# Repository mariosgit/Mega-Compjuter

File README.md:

# MEGA CompJU+TEr

# Status

Just an Idee. Made a basic PCB. Started experimenting...

# Wath's this ?

Arduino MEGA Shield with a UB8830 on top. The UB8833 is a Ostblock version of a Zilog Z8682 with a view quirks.

A bit like these things... http://8bitforce.com/projects/retroshield/ [Or here the Z80 code](https://gitlab.com/8bitforce/retroshield-arduino/-/blob/master/kz80/kz80_test/kz80_test.ino?ref_type=heads)

### Bugs / Improvements

* UB8833 reset(pin6) to some pin(45) ! keep it low until all ports initialize.
* LEDs for AS,RW,DS ?
* Fuse ? The Z8 needs 180mA !?

# Software

From Z8 datasheet...

* When AS goes LOW->HI latch the low adr byte. And read and keep RW flag.
* When DS goes HIGH->LOW and RW is reading (HIGH) put data on the bus. 
* When DS goes low and writing, read the data, do something e.g. save to ram.
* Turn of Data output ??? When ??? Read data to DS 1 hold time is 0, so turn it off after DS goes high.

### Reset

8833 RESET-Eingang (vgl . Kapitel 1) .
Hat er nach eingeschwungene r
Spannungs- und Taktversorgun g
für mindestens **18** Taktperiode n
Nullpegel, erzeugt er im Innere n
des Einchip-Mikrorechners einige
festgelegte Zustände . 

in kurzes Pro-
gramm ab %000C im Test-ROM
konfiguriert Port 0, Port 1 und
P34 für den Anschluß des exter-
nen Speichers und springt au f
Adresse %0812

Der UB 8830 D
(UB 8831 D) besitzt auch be i
„normalem” Rücksetzen die ge-
nannten Interruptvektoren un d
springt auf die Adresse %0812,
wenn dort kein RAM bestückt is t
und P32 keine Verbindung zu P35
hat. 

Der Einchip-
Mikrorechner besitzt ein Test-
programm im internen ROM,
das sich für unsere Zwecke gut
ausnutzen läßt. Damit es vom
Prozessor ausgeführt wird, muß
eine Drahtbrücke die Port
Anschlüsse P32 und P35 ver-
binden. .......  0-Impulse
mit einer Breite von 11 μs
erscheinen. Jede Abweichung
von dieser Regel deutet auf
eine Fehlverbindung zwischen
benachbarten Leiterzügen. Bei
Inbetriebnahme mit Kopfhörer
o. ä. müssen diese 16 An-
schlüsse mit gleichlauten 5,45-
kHz-Tönen 

Der laeuft mit 8mhz, auf dem Arduino mit 70khz, Faktor 114, 1254us.

### First something ?

after applying reset for at least 3 clocks it started doing things
* AS, DS, RW go up and down
* But no data on the bus !? -> could the thing be running it's internal ROM first ? Then there should be a addr=0x0800 (ext reset vector) comming up some time.. When it reads 0 it would start @0 again ???
* Oszi say it starts reading and writing to 0x1012 after about 173 initial clocks. it writes 0xff ?

# PCB

| ATMega Pin Port | UB8833 | Comments |
|---|---|---|
| PA | AdrHi | hi adr byte |
| PC | AdrLow/Data bus | multiplexed Data/Adr bus |
| | | |
| D2(int0) | AS | Adr strobe, Lo->Hi store the low adr |
| D3(int1) | DS | Data strobe, ?? |
| | | |
| D46/PL3(pwm pin) | XTAL | Clock |
| D47/PL2 | RW | Read/Write indication |

| ATMega Pin | Display |
|---|---|
| D53 | CS |
| D49 | DC |
| D51(mosi) | DI |
| D52(sclk) | CLK |

# Refs

https://github.com/boert/JU-TE-Computer

https://hc-ddr.hucki.net/wiki/doku.php/tiny/dokumentation 

https://www.robotrontechnik.de/html/forum/thwb/showtopic.php?threadid=16374

https://hackaday.com/2020/07/17/a-z80-board-with-very-few-parts/

http://bitsavers.informatik.uni-stuttgart.de/components/zilog/z8/Z8681_Data_Sheet_Mar83.pdf

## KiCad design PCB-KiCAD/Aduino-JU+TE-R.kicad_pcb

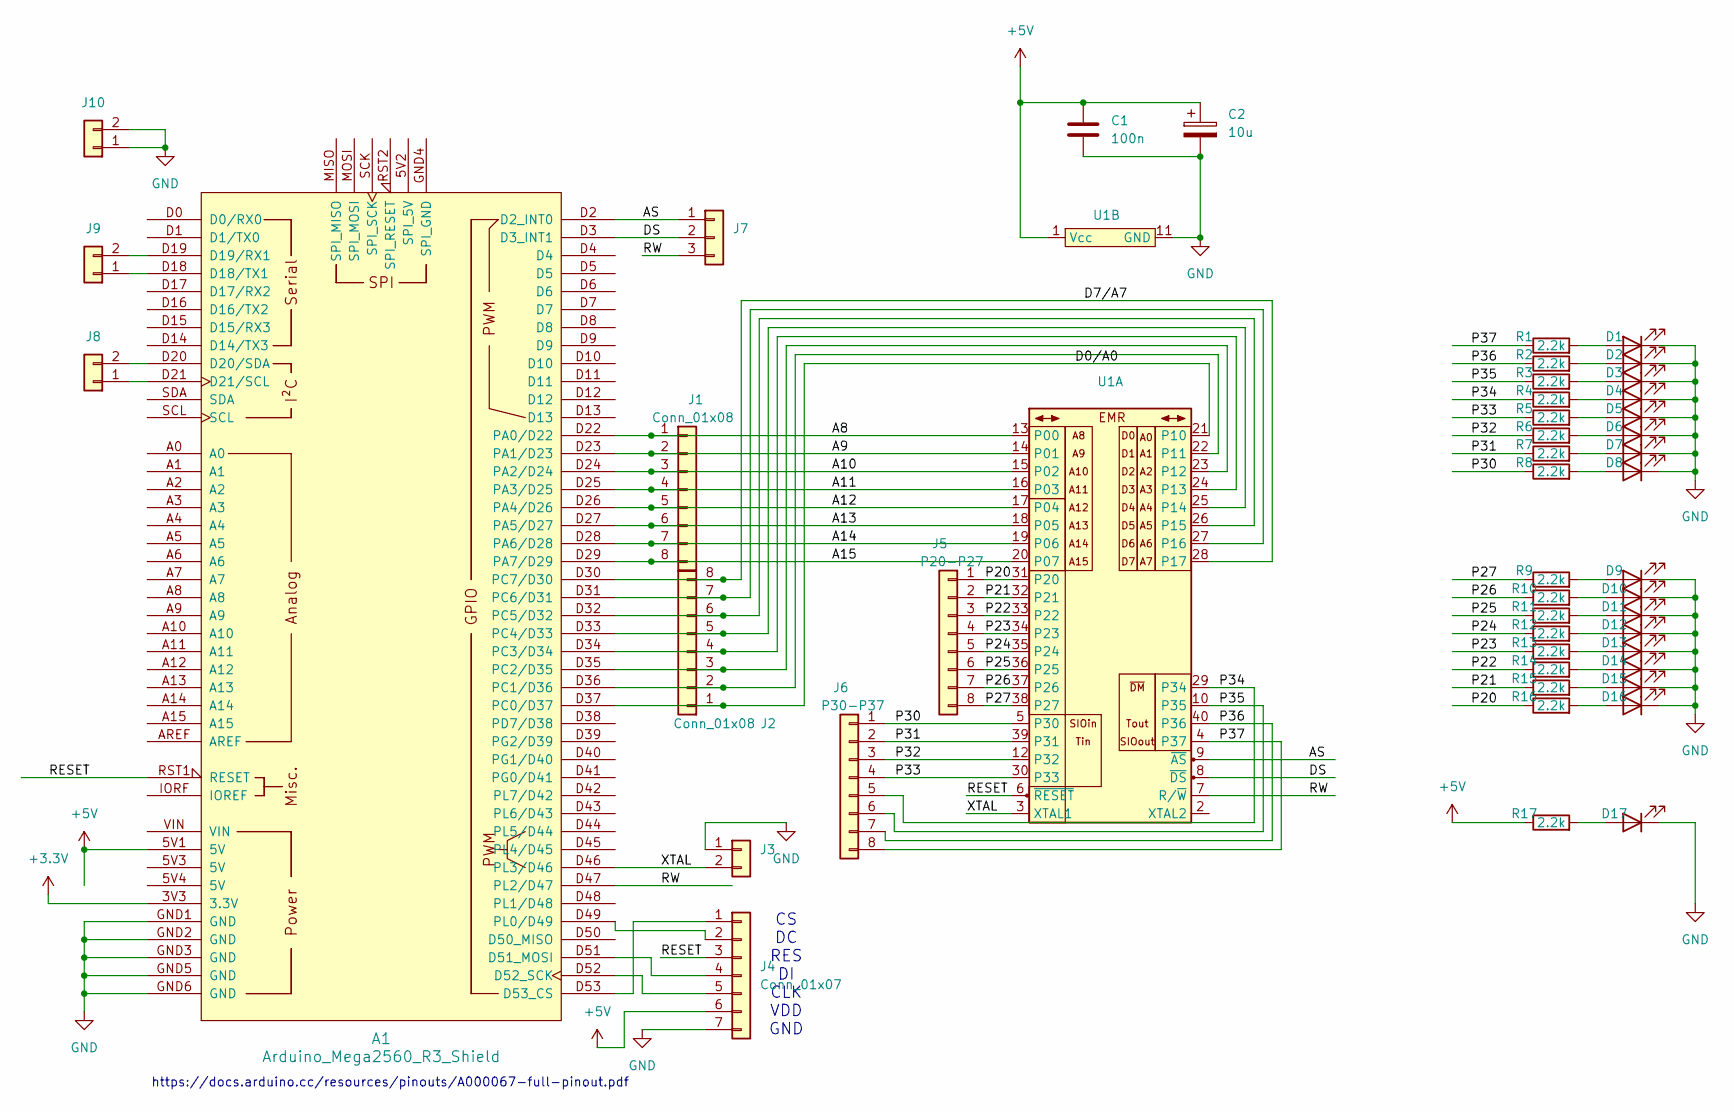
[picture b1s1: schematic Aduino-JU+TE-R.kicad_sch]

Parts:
A1: Arduino_Mega2560_R3_Shield
C1: 100n; C_0603_1608Metric_Pad1.08x0.95mm_HandSolder
C2: 10u; CP_EIA-2012-15_AVX-P_Pad1.30x1.05mm_HandSolder
D1, D2, D3, D4, D5, D6, D7, D8, D9, D10, D11, D12, D13, D14, D15, D16, D17: LED; LED_0603_1608Metric_Pad1.05x0.95mm_HandSolder
J1, J2: Conn_01x08; PinHeader_1x08_P2.54mm_Vertical
J3, J8, J9, J10: Conn_01x02; PinSocket_1x02_P2.54mm_Vertical
J4: Conn_01x07; PinHeader_1x07_P2.54mm_Vertical
J5: P20-P27; PinHeader_1x08_P2.54mm_Vertical
J6: P30-P37; PinHeader_1x08_P2.54mm_Vertical
J7: Conn_01x03; PinHeader_1x03_P2.54mm_Vertical
R1, R2, R3, R4, R5, R6, R7, R8, R9, R10, R11, R12, R13, R14, R15, R16, R17: 2.2k; R_0603_1608Metric_Pad0.98x0.95mm_HandSolder
U1: DIP-40_W15.24mm

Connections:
+3.3V: A1.3V3 (3.3V)
+5V: A1.5V1 (5V), C1.1, C2.1, J4.6, R17.1, U1.1 (Vcc)
/A8: A1.D22 (PA0/D22), J1.1, U1.13 (P00)
/A9: A1.D23 (PA1/D23), J1.2, U1.14 (P01)
/A10: A1.D24 (PA2/D24), J1.3, U1.15 (P02)
/A11: A1.D25 (PA3/D25), J1.4, U1.16 (P03)
/A12: A1.D26 (PA4/D26), J1.5, U1.17 (P04)
/A13: A1.D27 (PA5/D27), J1.6, U1.18 (P05)
/A14: A1.D28 (PA6/D28), J1.7, U1.19 (P06)
/A15: A1.D29 (PA7/D29), J1.8, U1.20 (P07)
/AS: A1.D2 (D2_INT0), J7.1, U1.9 (~AS)
/D0/A0: A1.D37 (PC0/D37), J2.1, U1.21 (P10)
/D7/A7: A1.D30 (PC7/D30), J2.8, U1.28 (P17)
/DS: A1.D3 (D3_INT1), J7.2, U1.8 (~DS)
/P20: J5.1, R16.1, U1.31 (P20)
/P21: J5.2, R15.1, U1.32 (P21)
/P22: J5.3, R14.1, U1.33 (P22)
/P23: J5.4, R13.1, U1.34 (P23)
/P24: J5.5, R12.1, U1.35 (P24)
/P25: J5.6, R11.1, U1.36 (P25)
/P26: J5.7, R10.1, U1.37 (P26)
/P27: J5.8, R9.1, U1.38 (P27)
/P30: J6.1, R8.1, U1.5 (P30)
/P31: J6.2, R7.1, U1.39 (P31)
/P32: J6.3, R6.1, U1.12 (P32)
/P33: J6.4, R5.1, U1.30 (P33)
/P34: J6.5, R4.1, U1.29 (P34)
/P35: J6.6, R3.1, U1.10 (P35)
/P36: J6.7, R2.1, U1.40 (P36)
/P37: J6.8, R1.1, U1.4 (P37)
/RESET: A1.RST1 (RESET), J4.3, U1.6 (~RESET)
/RW: A1.D47 (PL2/D47), J7.3, U1.7 (R/~W)
/XTAL: A1.D46 (PL3/D46), J3.2, U1.3 (XTAL1)
GND: A1.GND1 (GND), A1.GND2 (GND), A1.GND3 (GND), A1.GND5 (GND), A1.GND6 (GND), C1.2, C2.2, D1.1 (K), D2.1 (K), D3.1 (K), D4.1 (K), D5.1 (K), D6.1 (K), D7.1 (K), D8.1 (K), D9.1 (K), D10.1 (K), D11.1 (K), D12.1 (K), D13.1 (K), D14.1 (K), D15.1 (K), D16.1 (K), D17.1 (K), J3.1, J4.7, J10.1, J10.2, U1.11 (GND)
unnamed: A1.D18 (D18/TX1), J9.1
unnamed: A1.D19 (D19/RX1), J9.2
unnamed: A1.D20 (D20/SDA), J8.2
unnamed: A1.D21 (D21/SCL), J8.1
unnamed: A1.D51 (D51_MOSI), J4.4
unnamed: A1.D52 (D52_SCK), J4.5
unnamed: A1.D53 (D53_CS), J4.1
unnamed: A1.D36 (PC1/D36), J2.2, U1.22 (P11)
unnamed: A1.D35 (PC2/D35), J2.3, U1.23 (P12)
unnamed: A1.D34 (PC3/D34), J2.4, U1.24 (P13)
unnamed: A1.D33 (PC4/D33), J2.5, U1.25 (P14)
unnamed: A1.D32 (PC5/D32), J2.6, U1.26 (P15)
unnamed: A1.D31 (PC6/D31), J2.7, U1.27 (P16)
unnamed: A1.D49 (PL0/D49), J4.2
unnamed: D1.2 (A), R1.2
unnamed: D2.2 (A), R2.2
unnamed: D3.2 (A), R3.2
unnamed: D4.2 (A), R4.2
unnamed: D5.2 (A), R5.2
unnamed: D6.2 (A), R6.2
unnamed: D7.2 (A), R7.2
unnamed: D8.2 (A), R8.2
unnamed: D9.2 (A), R9.2
unnamed: D10.2 (A), R10.2
unnamed: D11.2 (A), R11.2
unnamed: D12.2 (A), R12.2
unnamed: D13.2 (A), R13.2
unnamed: D14.2 (A), R14.2
unnamed: D15.2 (A), R15.2
unnamed: D16.2 (A), R16.2
unnamed: D17.2 (A), R17.2

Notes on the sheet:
https://docs.arduino.cc/resources/pinouts/A000067-full-pinout.pdf
CS DC RES DI CLK VDD GND

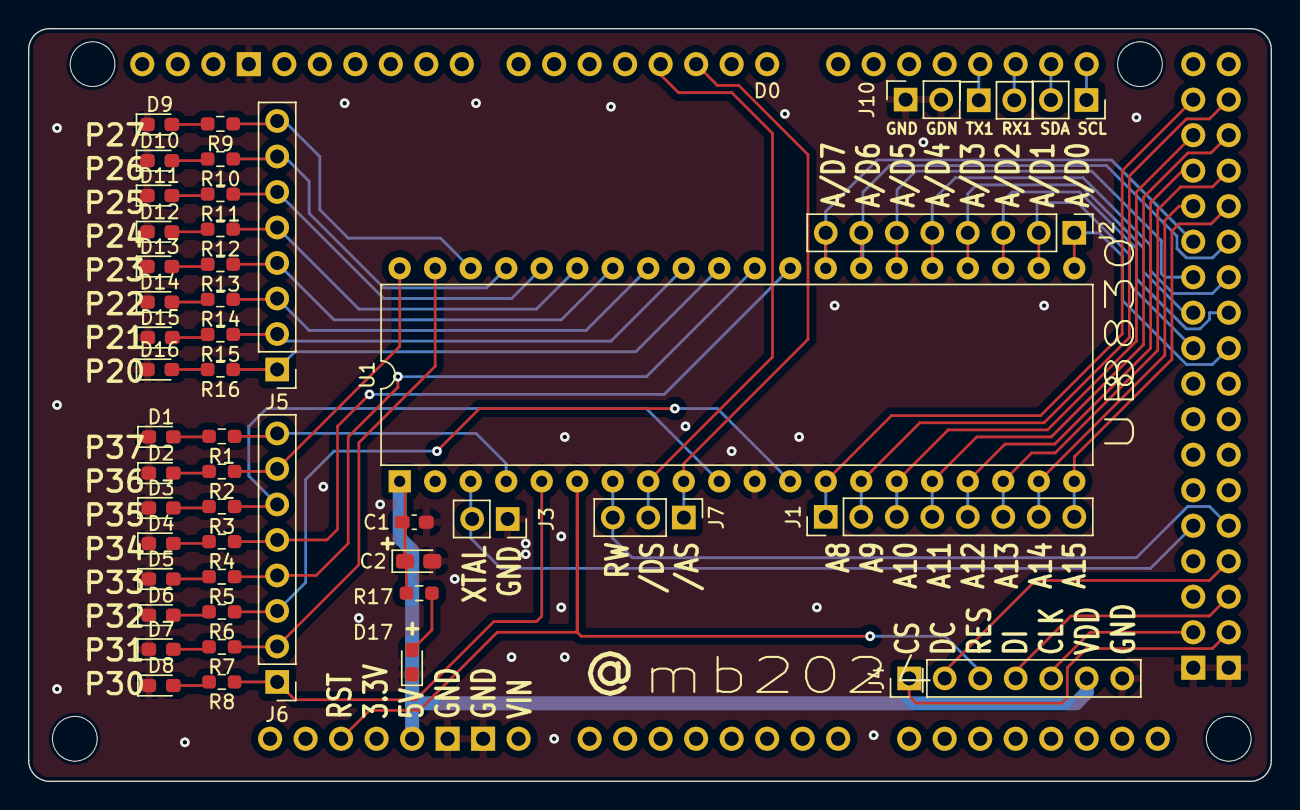
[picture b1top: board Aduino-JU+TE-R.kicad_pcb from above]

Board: 2 copper layers, 88.9 x 53.8 mm, 48 parts (0 on the bottom side), 64 nets.

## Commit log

2024-10-13 Started software.
2024-10-14 First try, no activity seen sofar.
2024-10-17 Some software experiments..
2024-10-17 Recherche..
